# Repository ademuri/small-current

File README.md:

# smallCurrent

This library is an adaptation of the circuit schematics of the
[tinyCurrent](https://github.com/nfhw/tinycurrent) project by n-fuse, which in
turn are adapted from [uCurrent
Gold](https://www.eevblog.com/projects/ucurrent/) by Dave Jones of EEVBlog.

This is functionally equivalent to the tinyCurrent. The BOM is optimized for
ordering from Digikey (easier to source the components in North America). It has
also been redesigned in the free and open-source KiCAD, rather than Altium, so
that making changes is more accessible.

## License

This work is licensed under a [Creative Commons Attribution-ShareAlike 3.0 Unported](https://creativecommons.org/licenses/by-sa/3.0/).

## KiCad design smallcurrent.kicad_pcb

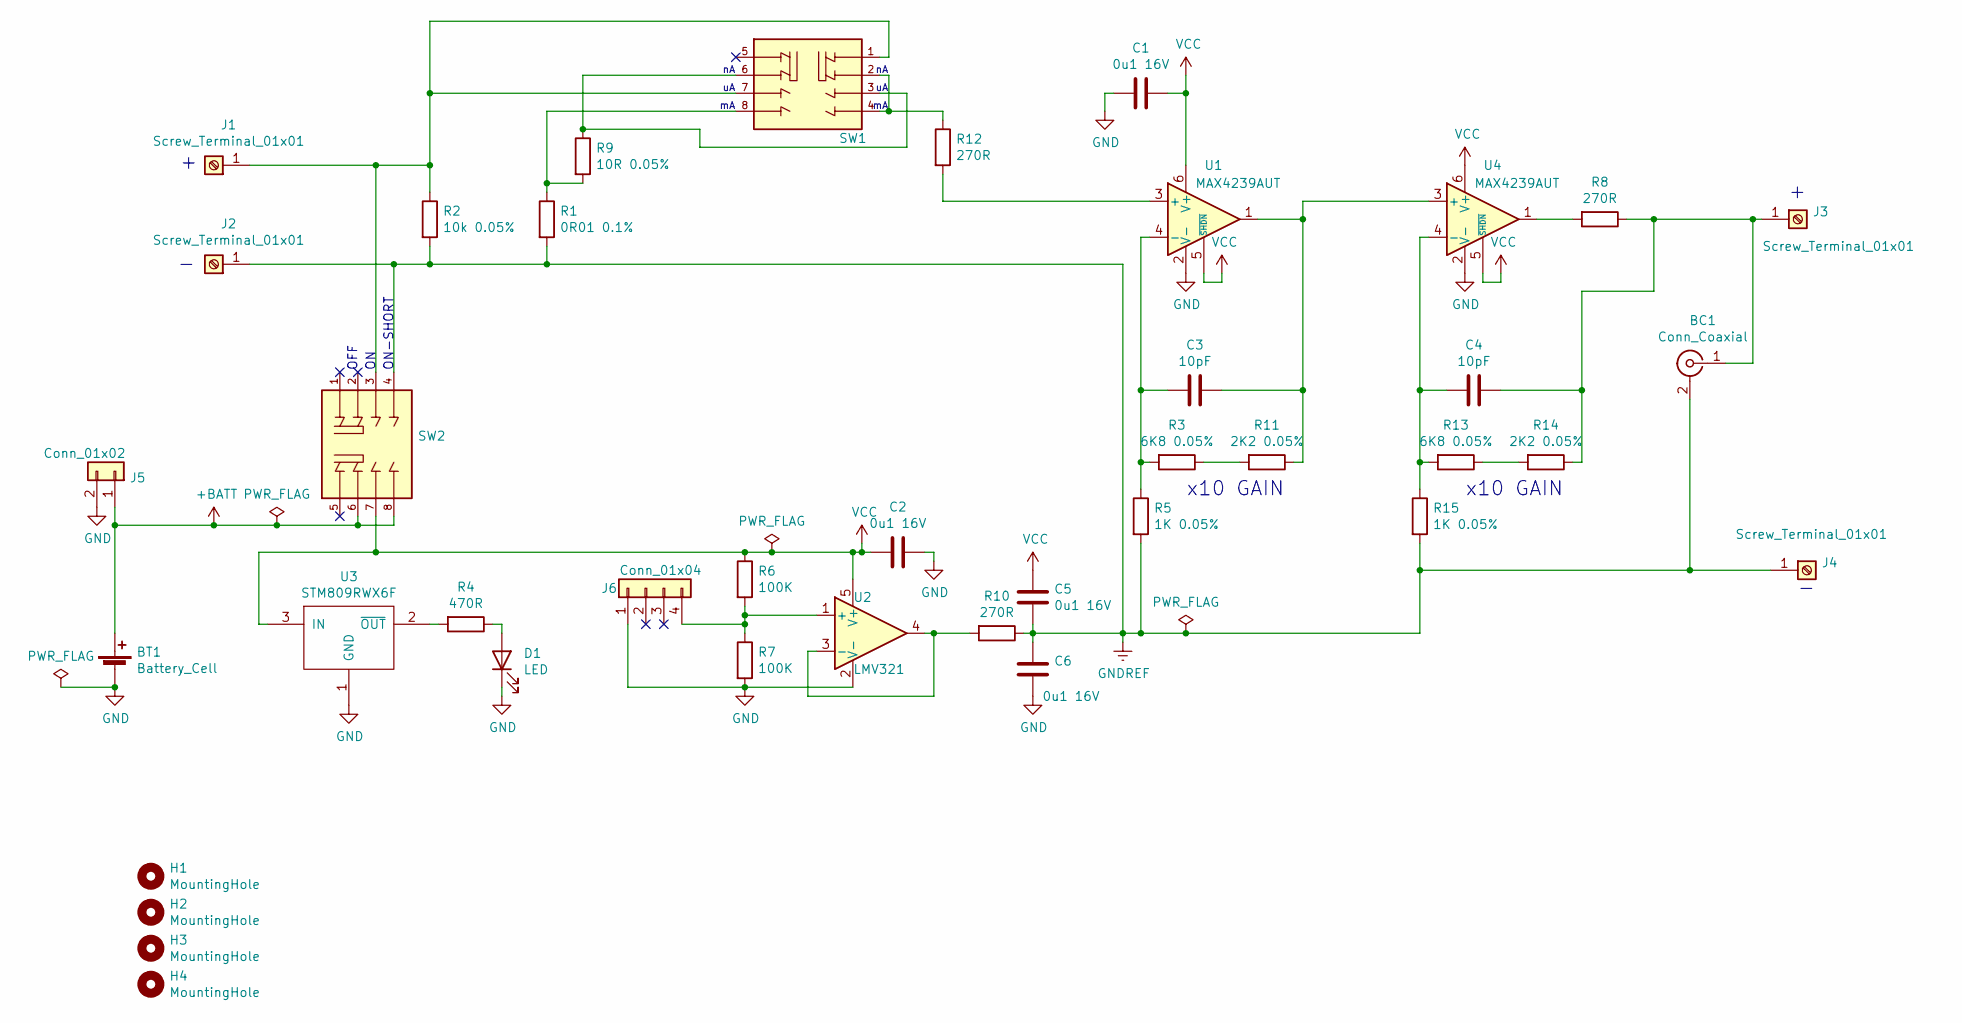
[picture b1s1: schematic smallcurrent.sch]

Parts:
BC1: Conn_Coaxial; TE_5-1634503-1
BT1: Battery_Cell; BAT_BS-7
C1, C2, C5, C6: 0u1 16V; C_0603_1608Metric
C3, C4: 10pF; C_0603_1608Metric
D1: LED; LED_D3.0mm
H1, H2, H3, H4: MountingHole; MountingHole_3.2mm_M3
J1, J2: Screw_Terminal_01x01; 111-0703-001_BANANA_BINDING_POST
J3, J4: Screw_Terminal_01x01; CT2230-BANANA-JACK
J5: Conn_01x02; Hirose_DF13-02P-1.25DSA_1x02_P1.25mm_Vertical
J6: Conn_01x04; PinSocket_1x04_P2.54mm_Vertical
R1: 0R01 0.1%; Y14870R01000B9R
R2: 10k 0.05%; R_0603_1608Metric
R3, R13: 6K8 0.05%; R_0603_1608Metric
R4: 470R; R_0603_1608Metric
R5, R15: 1K 0.05%; R_0603_1608Metric
R6, R7: 100K; R_0603_1608Metric
R8, R10, R12: 270R; R_0603_1608Metric
R9: 10R 0.05%; R_0805_2012Metric
R11, R14: 2K2 0.05%; R_0603_1608Metric
SW1: OS203013MT8QN1-snapeda-OS203013; SW_OS203013MT8QN1; PARTREV 8 aug 17
SW2: OS203013MT8QN1; SW_OS203013MT8QN1; PARTREV 8 aug 17
U1, U4: MAX4239AUT; SOT-23-6
U2: LMV321; SOT-23-5
U3: STM809RWX6F; SOT-23

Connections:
+BATT: BT1.1 (+), J5.1, SW2.6, SW2.8
GND: BT1.2 (-), C1.2, C2.1, C6.1, D1.1 (K), J5.2, J6.1, R7.2, U1.2 (V-), U2.2 (V-), U3.1 (GND), U4.2 (V-)
GNDREF: BC1.2 (Ext), BC1.3, BC1.4, BC1.5, C5.1, C6.2, J2.1, J4.1, R1.2, R2.2, R5.2, R10.1, R15.2, SW2.4
unnamed: BC1.1 (In), C4.2, J3.1, R8.1, R14.1
unnamed: C3.1, R3.2, R5.1, U1.4 (-)
unnamed: C3.2, R11.1, U1.1, U4.3 (+)
unnamed: C4.1, R13.2, R15.1, U4.4 (-)
unnamed: D1.2 (A), R4.1
unnamed: J1.1, R2.1, SW1.1, SW1.7, SW2.3
unnamed: J6.4, R6.2, R7.1, U2.1 (+)
unnamed: R1.1, R9.2, SW1.8
unnamed: R4.2, U3.2 (~OUT)
unnamed: R8.2, U4.1
unnamed: R9.1, SW1.3, SW1.6
unnamed: R10.2, U2.3 (-), U2.4
unnamed: R3.1, R11.2
unnamed: R12.1, SW1.2, SW1.4
unnamed: R12.2, U1.3 (+)
unnamed: R13.1, R14.2
VCC: C1.1, C2.2, C5.2, R6.1, SW2.7, U1.5 (~SHDN), U1.6 (V+), U2.5 (V+), U3.3 (IN), U4.5 (~SHDN), U4.6 (V+)

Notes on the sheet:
OFF
ON-SHORT
x10 GAIN

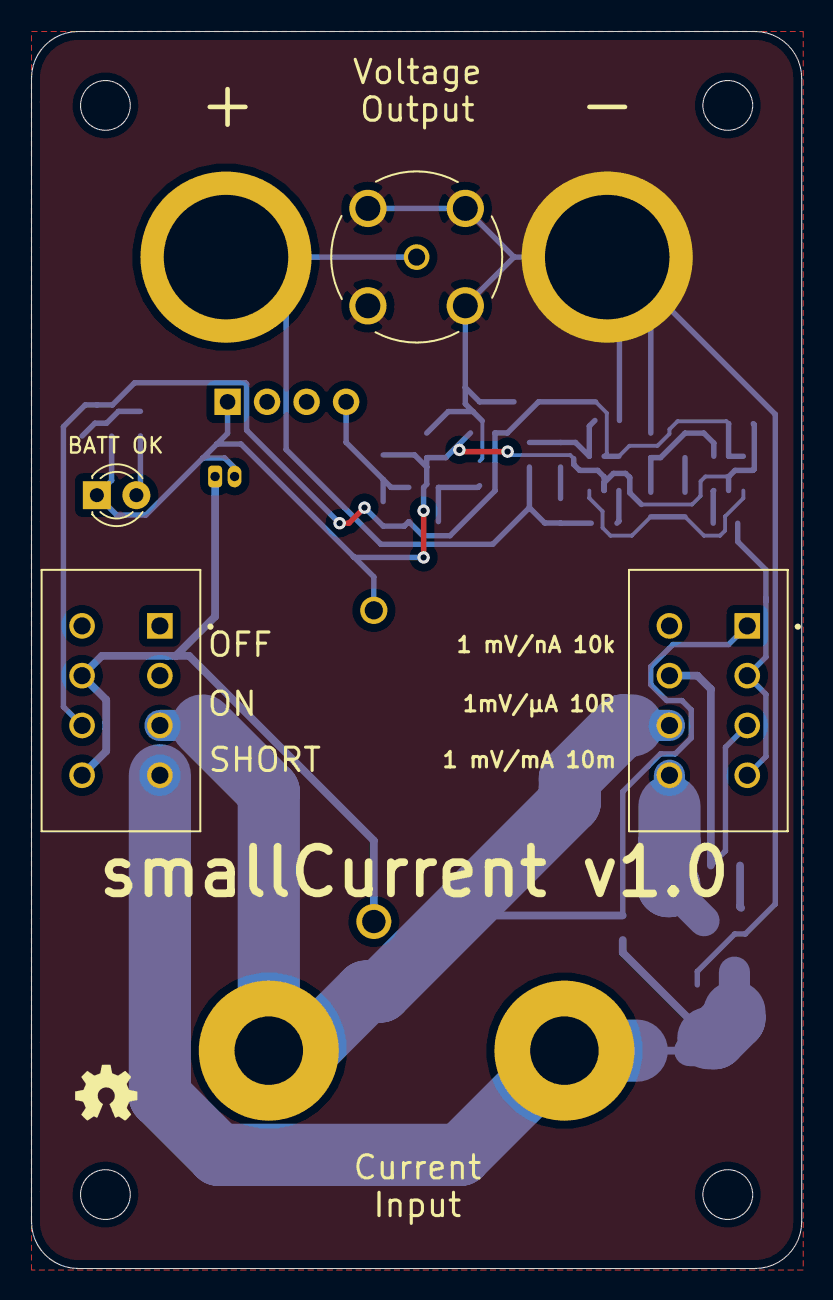
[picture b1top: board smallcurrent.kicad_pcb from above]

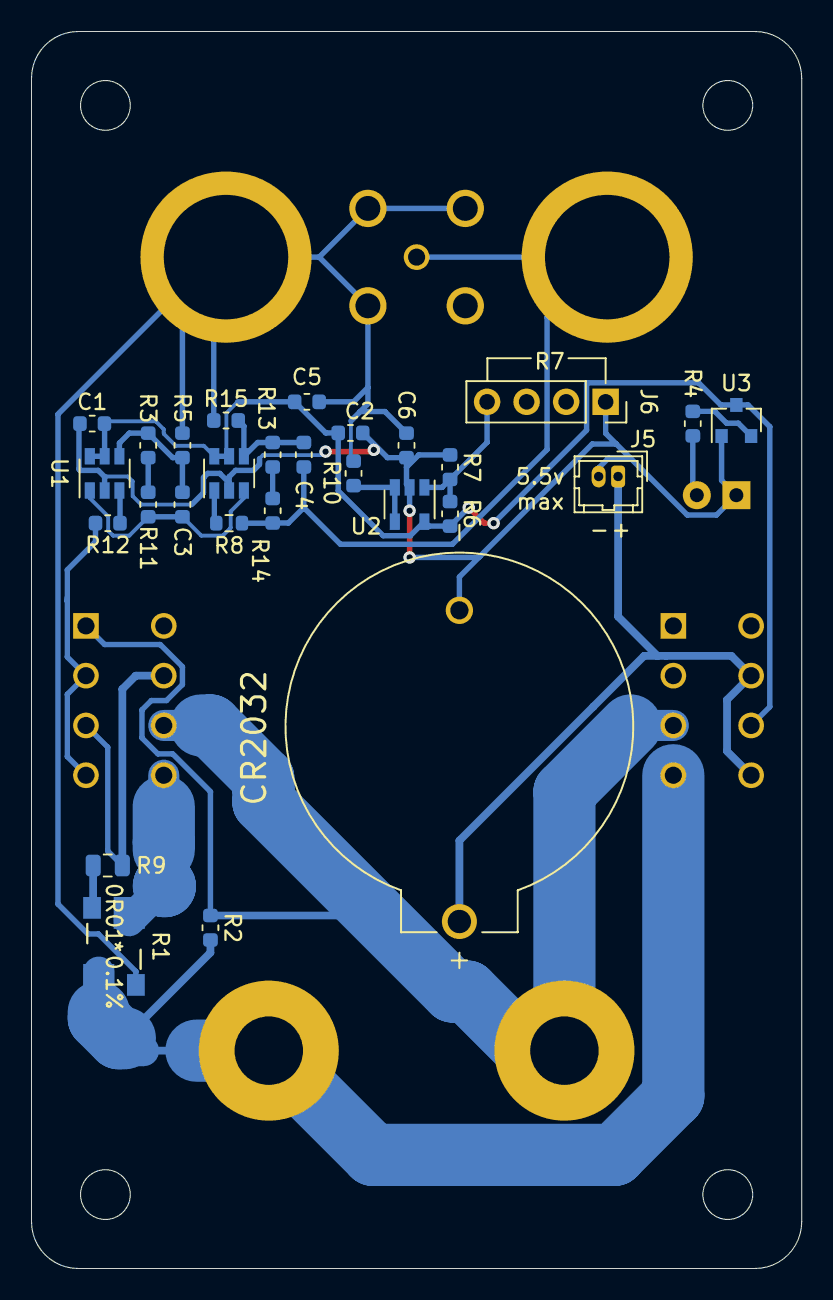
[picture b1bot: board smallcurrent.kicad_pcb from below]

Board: 2 copper layers, 49.5 x 79.5 mm, 40 parts (28 on the bottom side), 20 nets.

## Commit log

2020-11-21 Add schematic
2020-11-23 Add footprint associations
2020-11-23 Start layout
2020-11-25 More layout: most parts in position
2020-11-30 Version 1.0
2020-11-30 Add readme and license
2020-11-30 Add contributing
2020-12-10 Add interactive bom

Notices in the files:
parts and their libraries:
Copyright 2016 Accelerated Designs. All rights reserved.
